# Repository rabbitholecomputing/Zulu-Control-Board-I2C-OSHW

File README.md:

# Zulu Control Board V1.1 I2C OSHW
This design was originally created to control the ZuluIDE in a 5.25" bracket. It has been relicensed under the OSHW CERN OWL-S V2 see [LICENSE](LICENSE) for the community to spin their own version or produce this design themselves.

The design is created in KiCAD 9.  Gerber, BOM, and position files can be built automatically as a Github action.

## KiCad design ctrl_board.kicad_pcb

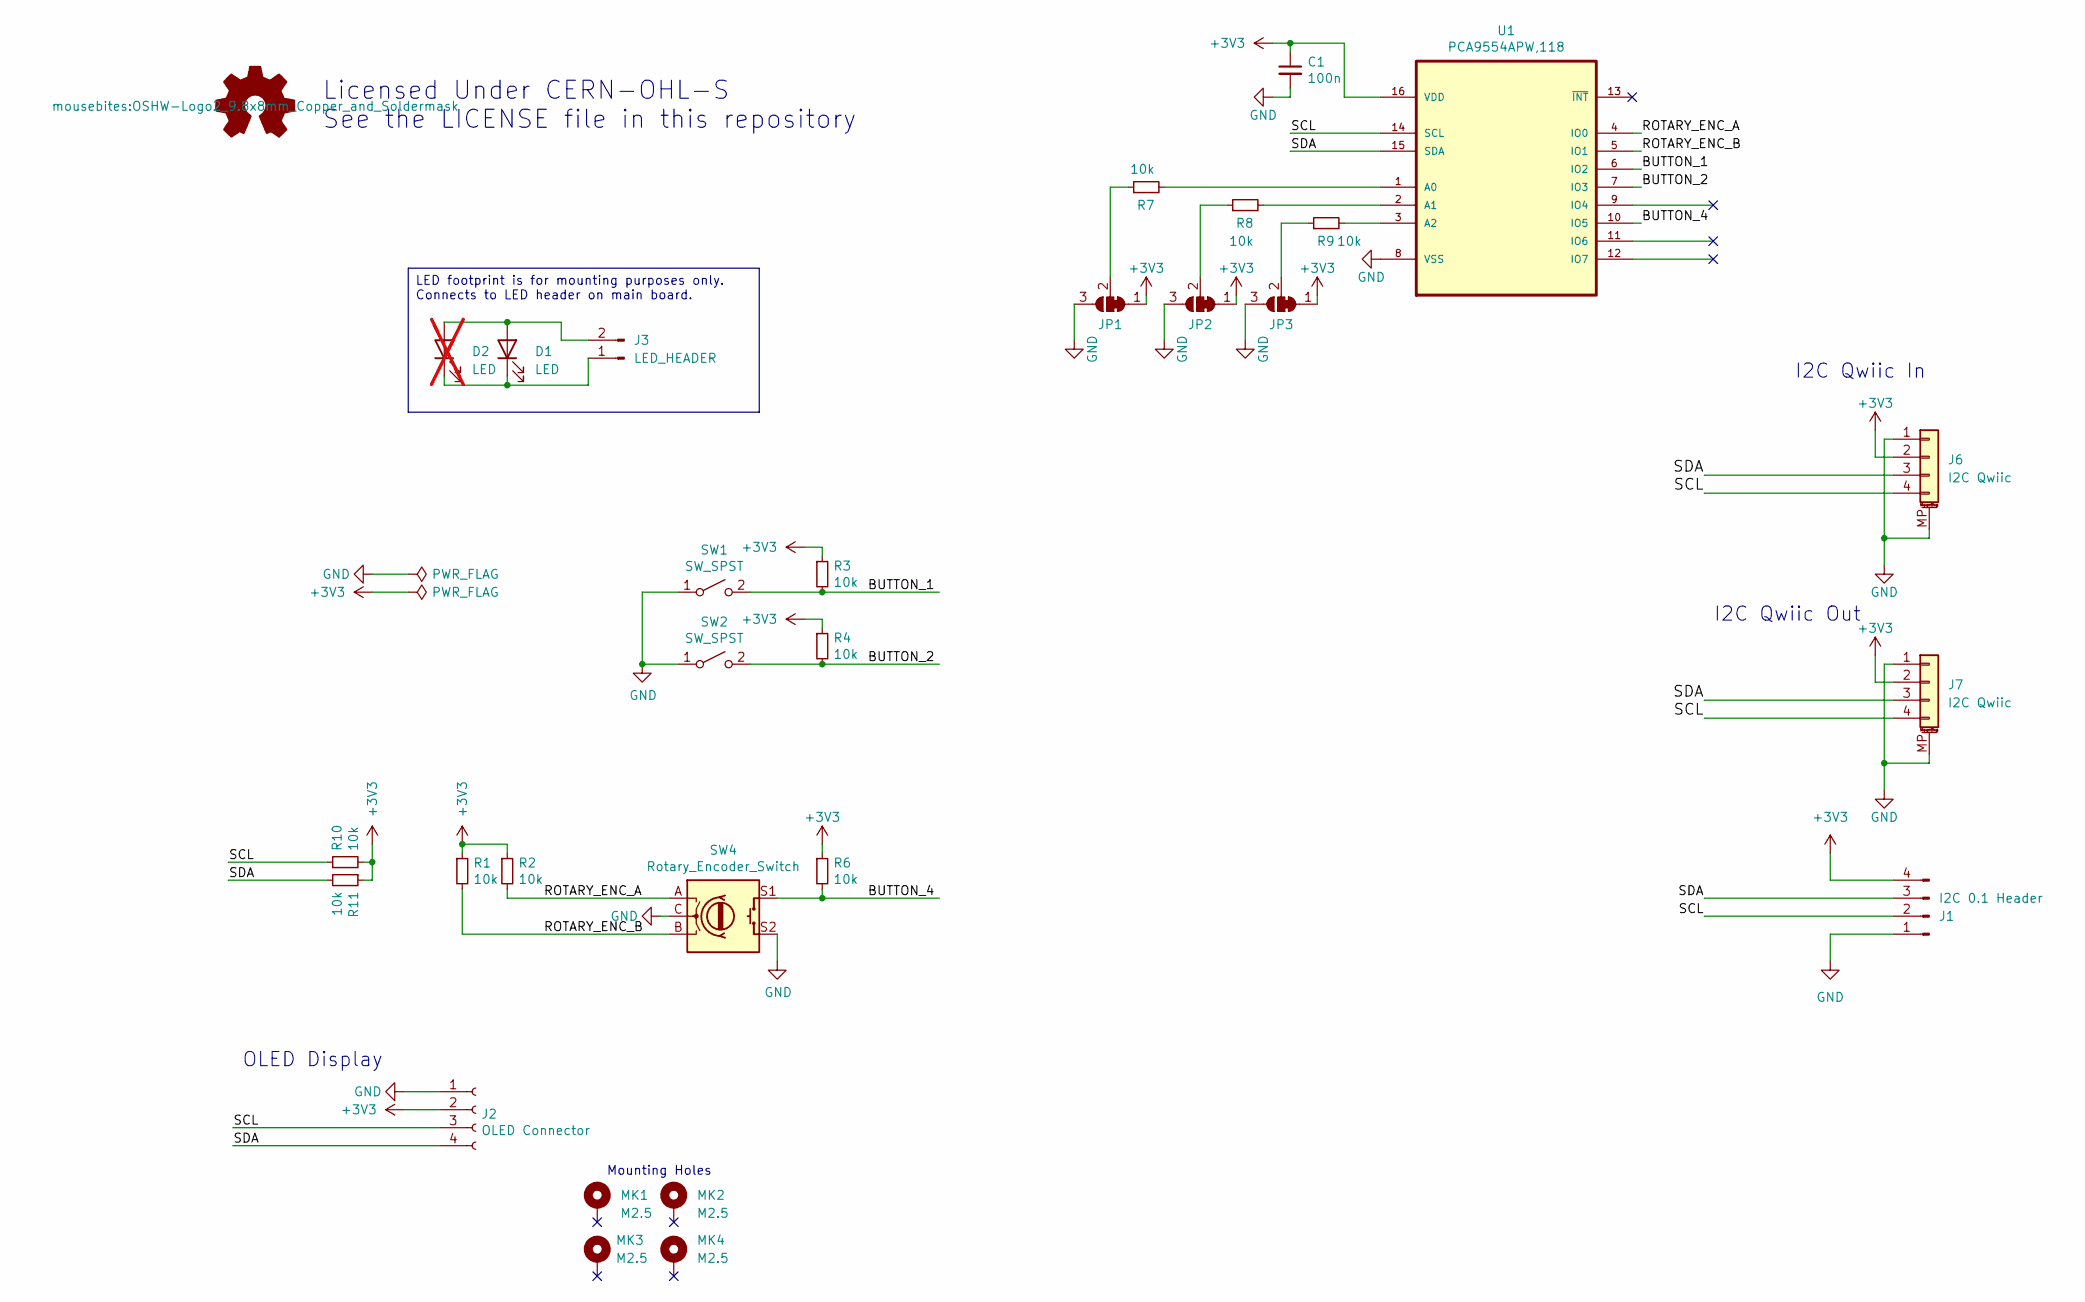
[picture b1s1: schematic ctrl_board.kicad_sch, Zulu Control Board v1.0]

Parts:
C1: 100n; C_0805_2012Metric; LCSC C49678
D1: LED; LED_D5.0mm
D2: LED; LED_1206_3216Metric_Pad1.42x1.75mm_HandSolder; not fitted
J1: I2C 0.1 Header; PinHeader_1x04_P2.54mm_Vertical
J2: OLED Connector; 0.9_and_1.3_in_OLED_Footprint
J3: LED_HEADER; PinHeader_1x02_P2.54mm_Vertical
J6, J7: I2C Qwiic; CONN4_BM04B-SRSS_JST; LCSC C160390
JP1, JP2, JP3: SolderJumper_3_Bridged12; SolderJumper-3_P1.3mm_Bridged12_RoundedPad1.0x1.5mm
MK1, MK2, MK3, MK4: M2.5; MountingHole_2.8mm_M2.5custom_DIN965_Pad
R1, R2, R3, R4, R6, R7, R8, R9, R10, R11: 10k; R_0805_2012Metric; LCSC C17414
SW1, SW2: SW_SPST; SW_PUSH_6mm_H5mm; LCSC C110153
SW4: Rotary_Encoder_Switch; RotaryEncoder_Bourns_PEC12R-4225F-S0024_H25mm; MPN PEC12R-4225F-S0024; LCSC C5331618
SYM1: Logo_Open_Hardware_Small; OSHW-Logo2_9.8x8mm_Copper_and_Soldermask
U1: PCA9554APW,118; TSSOP-16_4.4x5mm_P0.65mm; MPN PCA9554APW,118; LCSC C86803

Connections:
+3V3: C1.1, J1.4, J2.2, J6.2, J7.2, JP1.1 (A), JP2.1 (A), JP3.1 (A), R1.1, R2.1, R3.1, R4.1, R6.1, R10.2, R11.1, U1.16 (VDD)
/BUTTON_1: R3.2, SW1.2 (B), U1.6 (IO2)
/BUTTON_2: R4.2, SW2.2 (B), U1.7 (IO3)
/BUTTON_4: R6.2, SW4.S1, U1.10 (IO5)
/ROTARY_ENC_A: R2.2, SW4.A, U1.4 (IO0)
/ROTARY_ENC_B: R1.2, SW4.B, U1.5 (IO1)
/SCL: J1.2, J2.3, J6.4, J7.4, R10.1, U1.14 (SCL)
/SDA: J1.3, J2.4, J6.3, J7.3, R11.2, U1.15 (SDA)
GND: C1.2, J1.1, J2.1, J6.1, J6.MP (MountPin), J7.1, J7.MP (MountPin), JP1.3 (B), JP2.3 (B), JP3.3 (B), SW1.1 (A), SW2.1 (A), SW4.C, SW4.S2, U1.8 (VSS)
unnamed: D1.2 (A), D2.2 (A), J3.2
unnamed: D1.1 (K), D2.1 (K), J3.1
unnamed: JP1.2 (C), R7.1
unnamed: JP2.2 (C), R8.1
unnamed: JP3.2 (C), R9.1
unnamed: R7.2, U1.1 (A0)
unnamed: R8.2, U1.2 (A1)
unnamed: R9.2, U1.3 (A2)

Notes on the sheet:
I2C Qwiic In
I2C Qwiic Out
OLED Display
Mounting Holes
Licensed Under CERN-OHL-S See the LICENSE file in this repository
LED footprint is for mounting purposes only. Connects to LED header on main board.

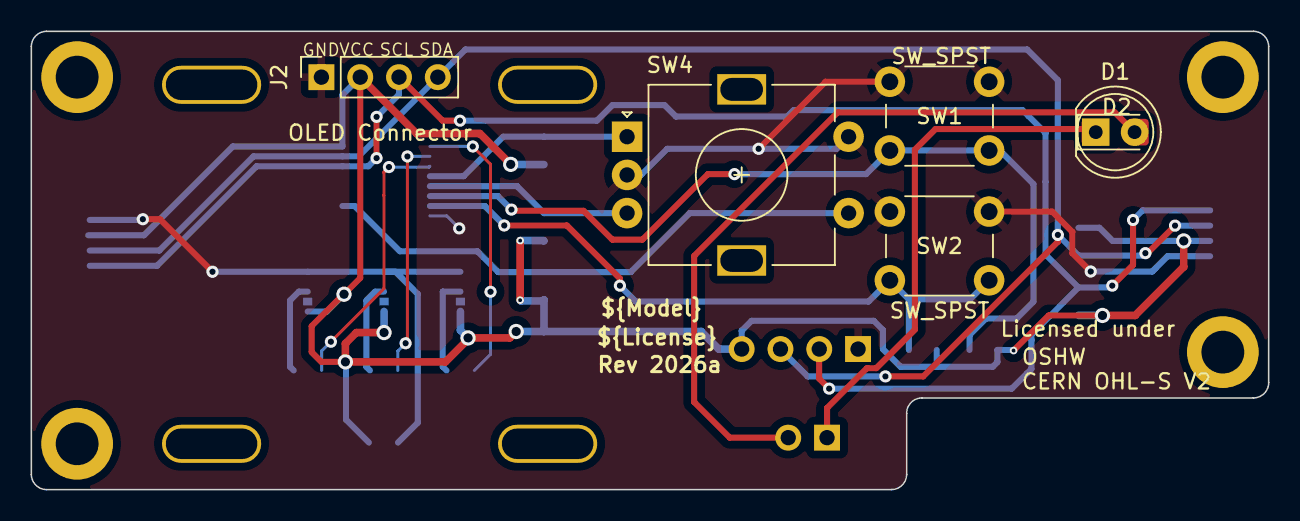
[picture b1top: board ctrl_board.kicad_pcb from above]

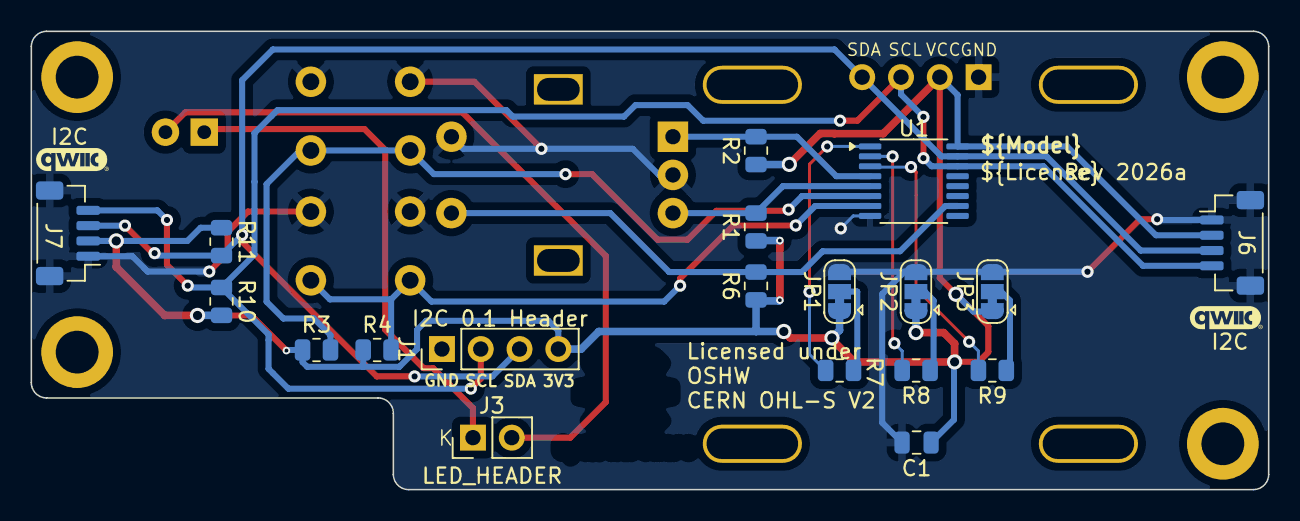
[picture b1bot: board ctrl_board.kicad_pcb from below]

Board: 2 copper layers, 81.0 x 30.0 mm, 30 parts (20 on the bottom side), 17 nets.

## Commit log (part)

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2026-03-05 Fix grammatical error in README.md
2026-03-05 Add PCB renders of front and back, link from README

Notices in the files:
ctrl_board.kicad_pcb:
CERN OHL-S V2
parts and their libraries:
Copyright: © 2026 Rabbit Hole Computing LLC
License: OSHW
